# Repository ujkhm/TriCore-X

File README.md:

# Xeltri

> **Xeltri: a heterogeneous development board.**
> X = mixed heterogeneous cores, el = electronics, tri = three cores (MPU + MCU + FPGA).
> This board puts an FPGA, an MPU, and an MCU on one system. (in development)

#### Read the original Traditional Chinese version [here](README.zh-TW.md).

**Hackaday.io Project Page:** [Xeltri - Pick and Place Control Board](https://hackaday.io/project/206451-xeltri-pick-and-place-control-board)

---

### Project overview
This project is a main controller board built for a desktop pick-and-place (PnP) machine. The three cores — STM32H745XIH6 (MCU), XC7A35T-2CSG325C (FPGA), and V851S (MPU) — are locked in and work together. Expansion I/O so far: PCIe 2.1 ×2 (in a PCIe ×4 slot, wired to the FPGA) and a microSD card slot. Everything else is still TBD.

---

### How it started
I needed a pick-and-place machine, but buying one was too expensive, so I decided to build it myself. I was 15 when I started (25 June 2026). It began as a sudden “what if I just try?” thought, and I then committed to it as a long-term project. A lot of what this board needs is something I only know *what it is for*, not something I have actually designed before. I know this is hard, so please keep expectations modest — but it should not be terrible either.

---

### Board architecture and why these cores
Xeltri is built around STM32H745XIH6 (MCU), XC7A35T-2CSG325C (FPGA), and V851S (MPU). I chose this trio because I want to try mixed alignment: pure optical alignment for simple parts (0805, 0402, and similar packages), and a vision camera (OpenCV-style) for complex parts. I also want up-looking / down-looking cameras plus on-device AI for machine-health checks — that is why V851S is in the mix.

I am using pure optical alignment on simple parts because I want industrial on-the-fly (“flying shot”) speed, and the vision hardware that can actually do that is far too expensive. Optical alignment is much cheaper, but it needs real-time performance. The machine is meant to be a box-style CoreXY so it takes less floor space (like a Voron printer), which means a lot of structure and a lot of stepper motors to control. Closed-loop steppers with the servo drive in the motor base are too expensive for me, and the cheap ones are not fast enough. An FPGA can handle that and more — I want the finished machine to be strong, not merely usable. That is how this three-core combination ended up here.

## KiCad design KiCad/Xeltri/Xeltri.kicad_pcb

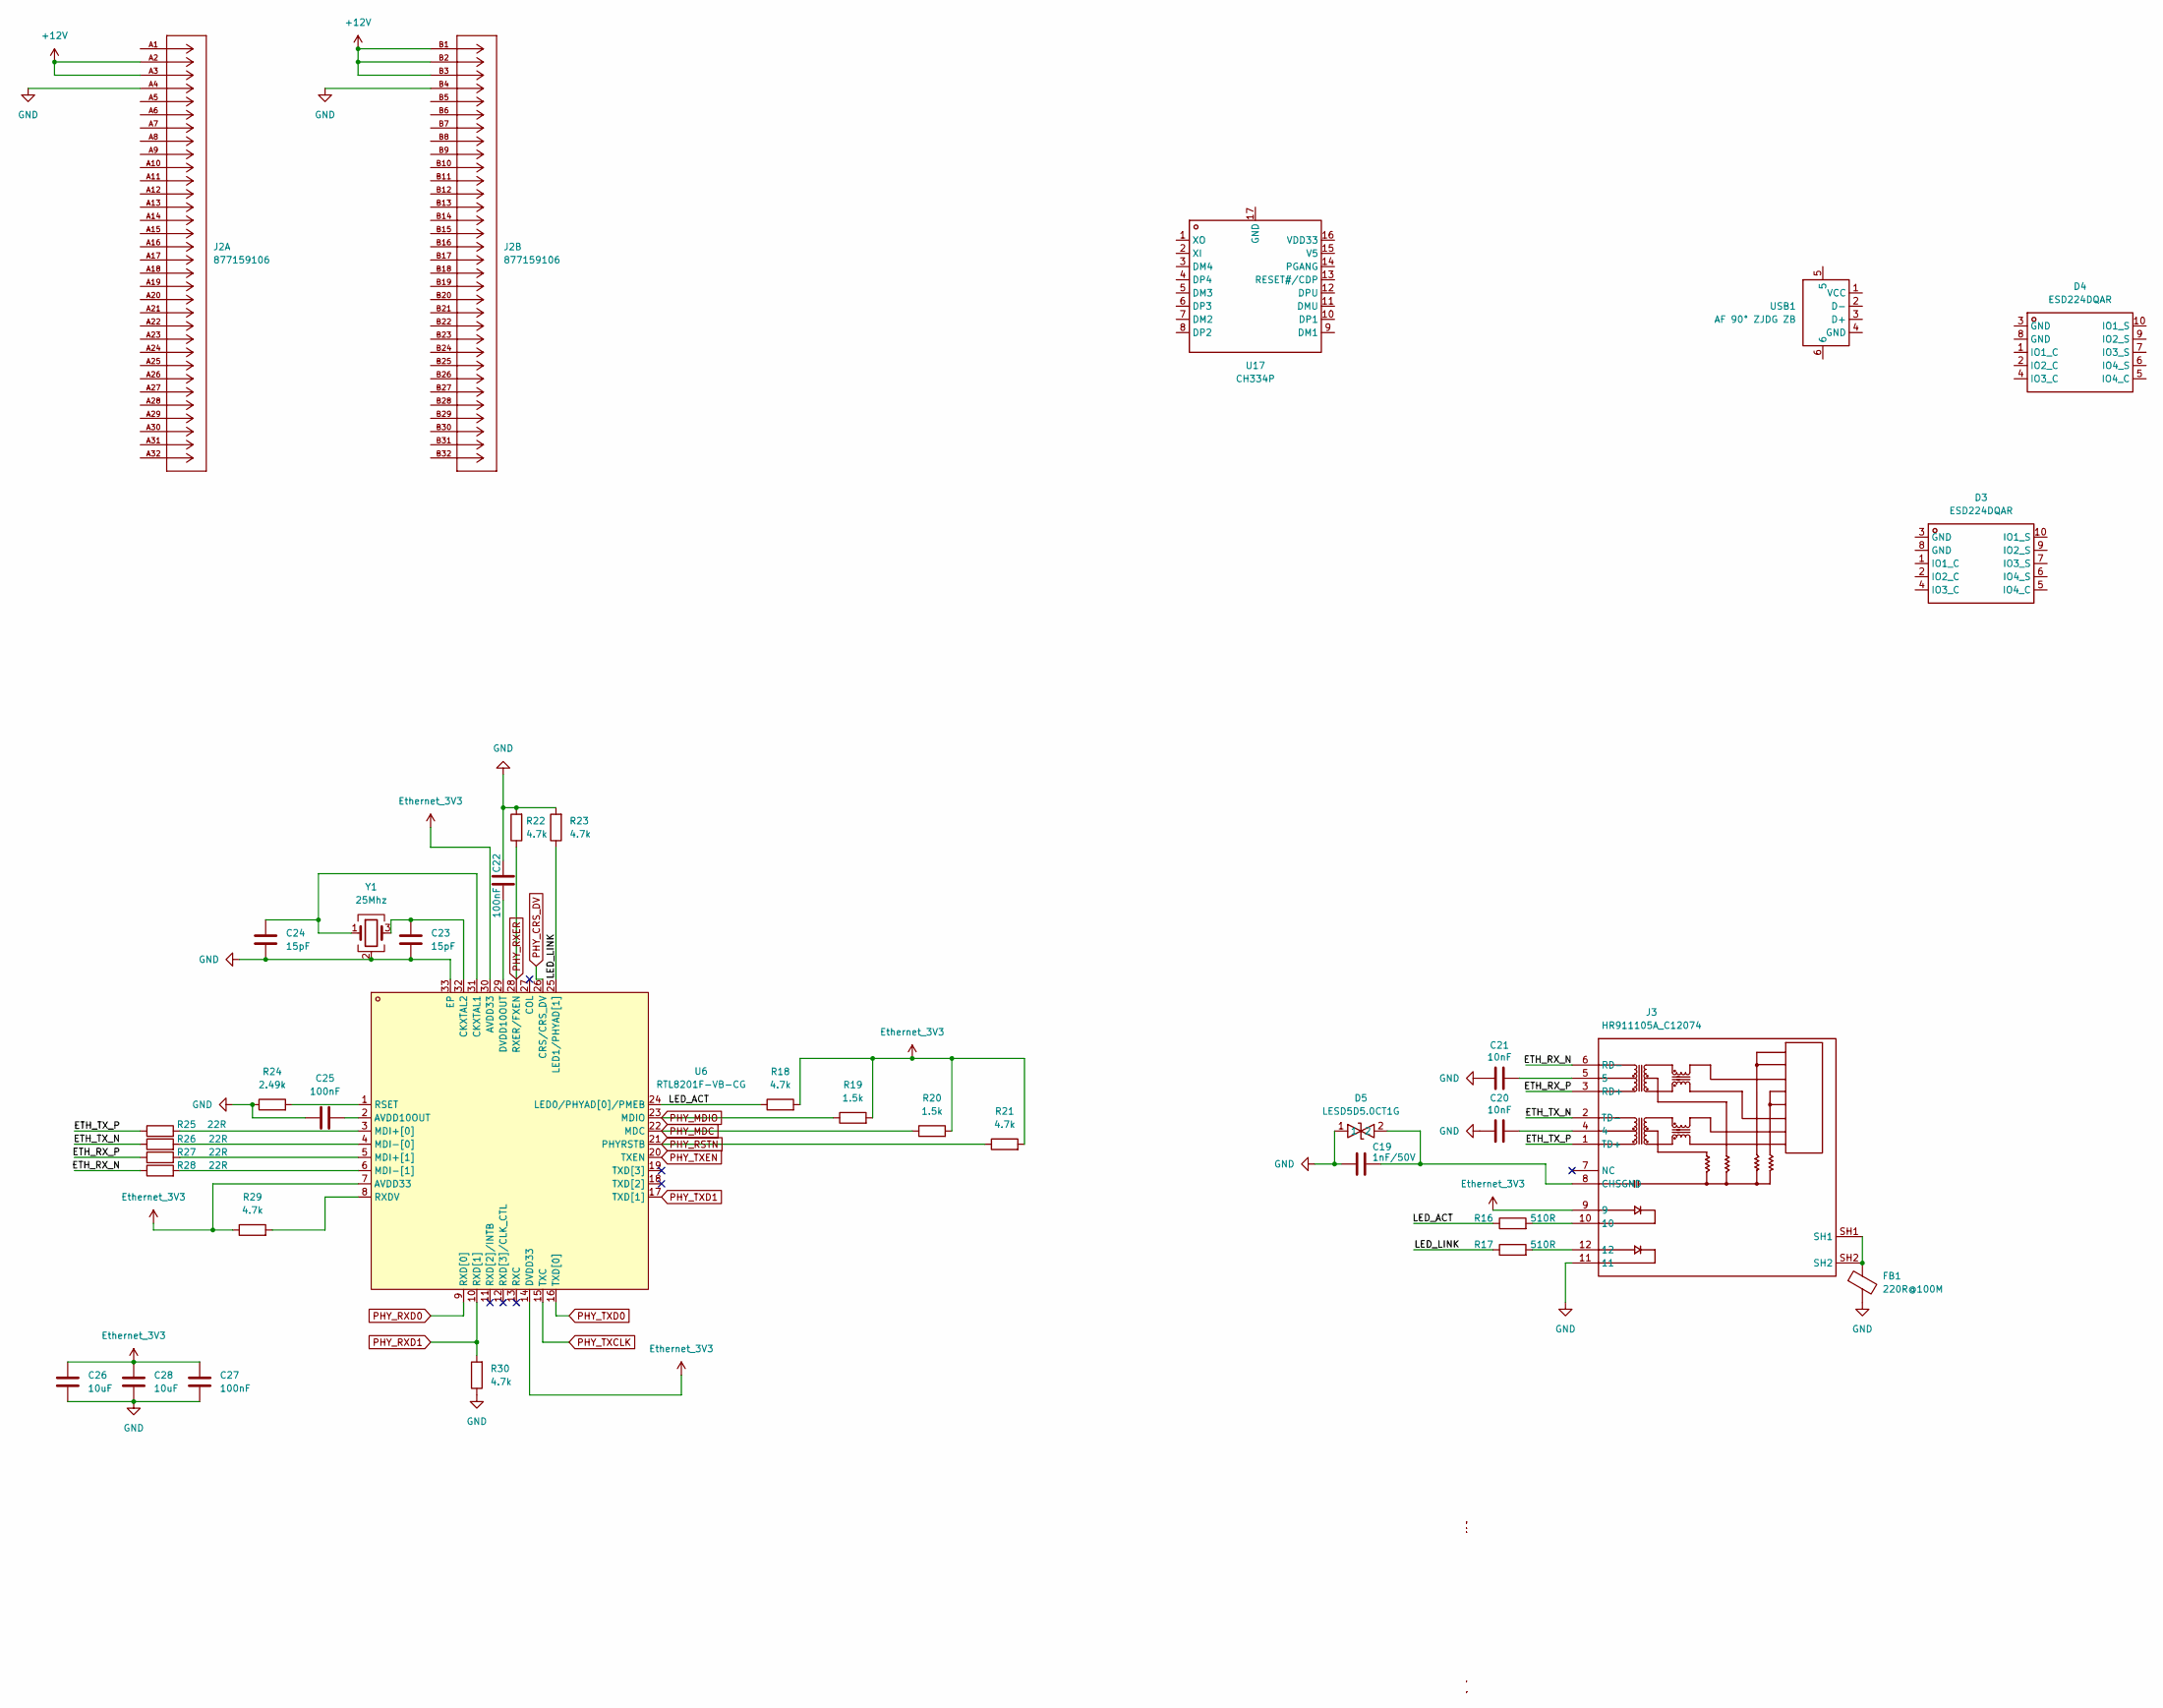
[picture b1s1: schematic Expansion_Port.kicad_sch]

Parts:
C19: 1nF/50V; C_0402_1005Metric
C20, C21: 10nF; C_0402_1005Metric
C22, C25, C27: 100nF; C_0402_1005Metric
C23, C24: 15pF; C_0402_1005Metric
C26, C28: 10uF; C_0402_1005Metric
D3, D4: ESD224DQAR; USON-10_L2.5-W1.0-P0.50-BL; LCSC Part C1981316
D5: LESD5D5.0CT1G; SOD-523_L1.2-W0.8-LS1.6-BI; LCSC Part C383211
FB1: 220R@100M; L_0603_1608Metric
J2: 877159106; CONN_87715-9106_MOL; MANUFACTURER_PART_NUMBER 877159106
J3: HR911105A_C12074; RJ45-TH_HR911105A; LCSC Part C12074
R16, R17: 510R; R_0402_1005Metric
R18, R21, R22, R23, R29, R30: 4.7k; R_0402_1005Metric
R19, R20: 1.5k; R_0402_1005Metric
R24: 2.49k; R_0402_1005Metric
R25, R26, R27, R28: 22R; R_0402_1005Metric
U6: RTL8201F-VB-CG; QFN-32_L5.0-W5.0-P0.50-BL-EP3.4; MPN RTL8201F-VB-CG; LCSC Part C45044
U17: CH334P; QFN-16_L3.0-W3.0-P0.50-BL-EP1.7; LCSC Part C5373042
USB1: AF 90° ZJDG ZB; USB-A-TH_AF-90-ZJDG-ZB; LCSC Part C6332182
Y1: 25Mhz; Crystal_SMD_3225-4Pin_3.2x2.5mm

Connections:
+12V: J2.A2, J2.A3, J2.B1, J2.B2, J2.B3; also elsewhere on the board
/Expansion_Port/ETH_RX_N: J3.6 (RD-), R28.1
/Expansion_Port/ETH_RX_P: J3.3 (RD+), R27.1
/Expansion_Port/ETH_TX_N: J3.2 (TD-), R26.1
/Expansion_Port/ETH_TX_P: J3.1 (TD+), R25.1
/Expansion_Port/LED_ACT: R16.1, R18.1, U6.24 (LED0/PHYAD[0]/PMEB)
/Expansion_Port/LED_LINK: R17.1, R23.1, U6.25 (LED1/PHYAD[1])
Ethernet_3V3: C26.1, C27.1, C28.1, J3.9, R18.2, R19.2, R20.2, R21.2, R29.1, U6.7 (AVDD33), U6.14 (DVDD33), U6.30 (AVDD33)
GND: C19.1, C20.1, C21.1, C22.2, C23.1, C24.1, C25.1, C26.2, C27.2, C28.2, D5.1, FB1.2, J2.A4, J2.B4, J3.11, R22.2, R23.2, R24.1, R30.1, U6.33 (EP), Y1.2 (G), Y1.4 (G); also elsewhere on the board
unnamed: C20.2, J3.4
unnamed: C21.2, J3.5
unnamed: FB1.1, J3.SH1, J3.SH2
unnamed: C19.2, D5.2, J3.8 (CHSGND)
unnamed: J3.10, R16.2
unnamed: J3.12, R17.2
unnamed: C25.2, U6.2 (AVDD10OUT)
unnamed: C24.2, U6.31 (CKXTAL1), Y1.1
unnamed: C23.2, U6.32 (CKXTAL2), Y1.3
unnamed: C22.1, U6.29 (DVDD10OUT)
unnamed: R25.2, U6.3 (MDI+[0])
unnamed: R27.2, U6.5 (MDI+[1])
unnamed: R26.2, U6.4 (MDI-[0])
unnamed: R28.2, U6.6 (MDI-[1])
unnamed: R24.2, U6.1 (RSET)
unnamed: R29.2, U6.8 (RXDV)
PHY_CRS_DV: U6.26 (CRS/CRS_DV)
PHY_MDC: R20.1, U6.22 (MDC)
PHY_MDIO: R19.1, U6.23 (MDIO)
PHY_RSTN: R21.1, U6.21 (PHYRSTB)
PHY_RXD0: U6.9 (RXD[0])
PHY_RXD1: R30.2, U6.10 (RXD[1])
PHY_RXER: R22.1, U6.28 (RXER/FXEN)
PHY_TXCLK: U6.15 (TXC)
PHY_TXD0: U6.16 (TXD[0])
PHY_TXD1: U6.17 (TXD[1])
PHY_TXEN: U6.20 (TXEN)

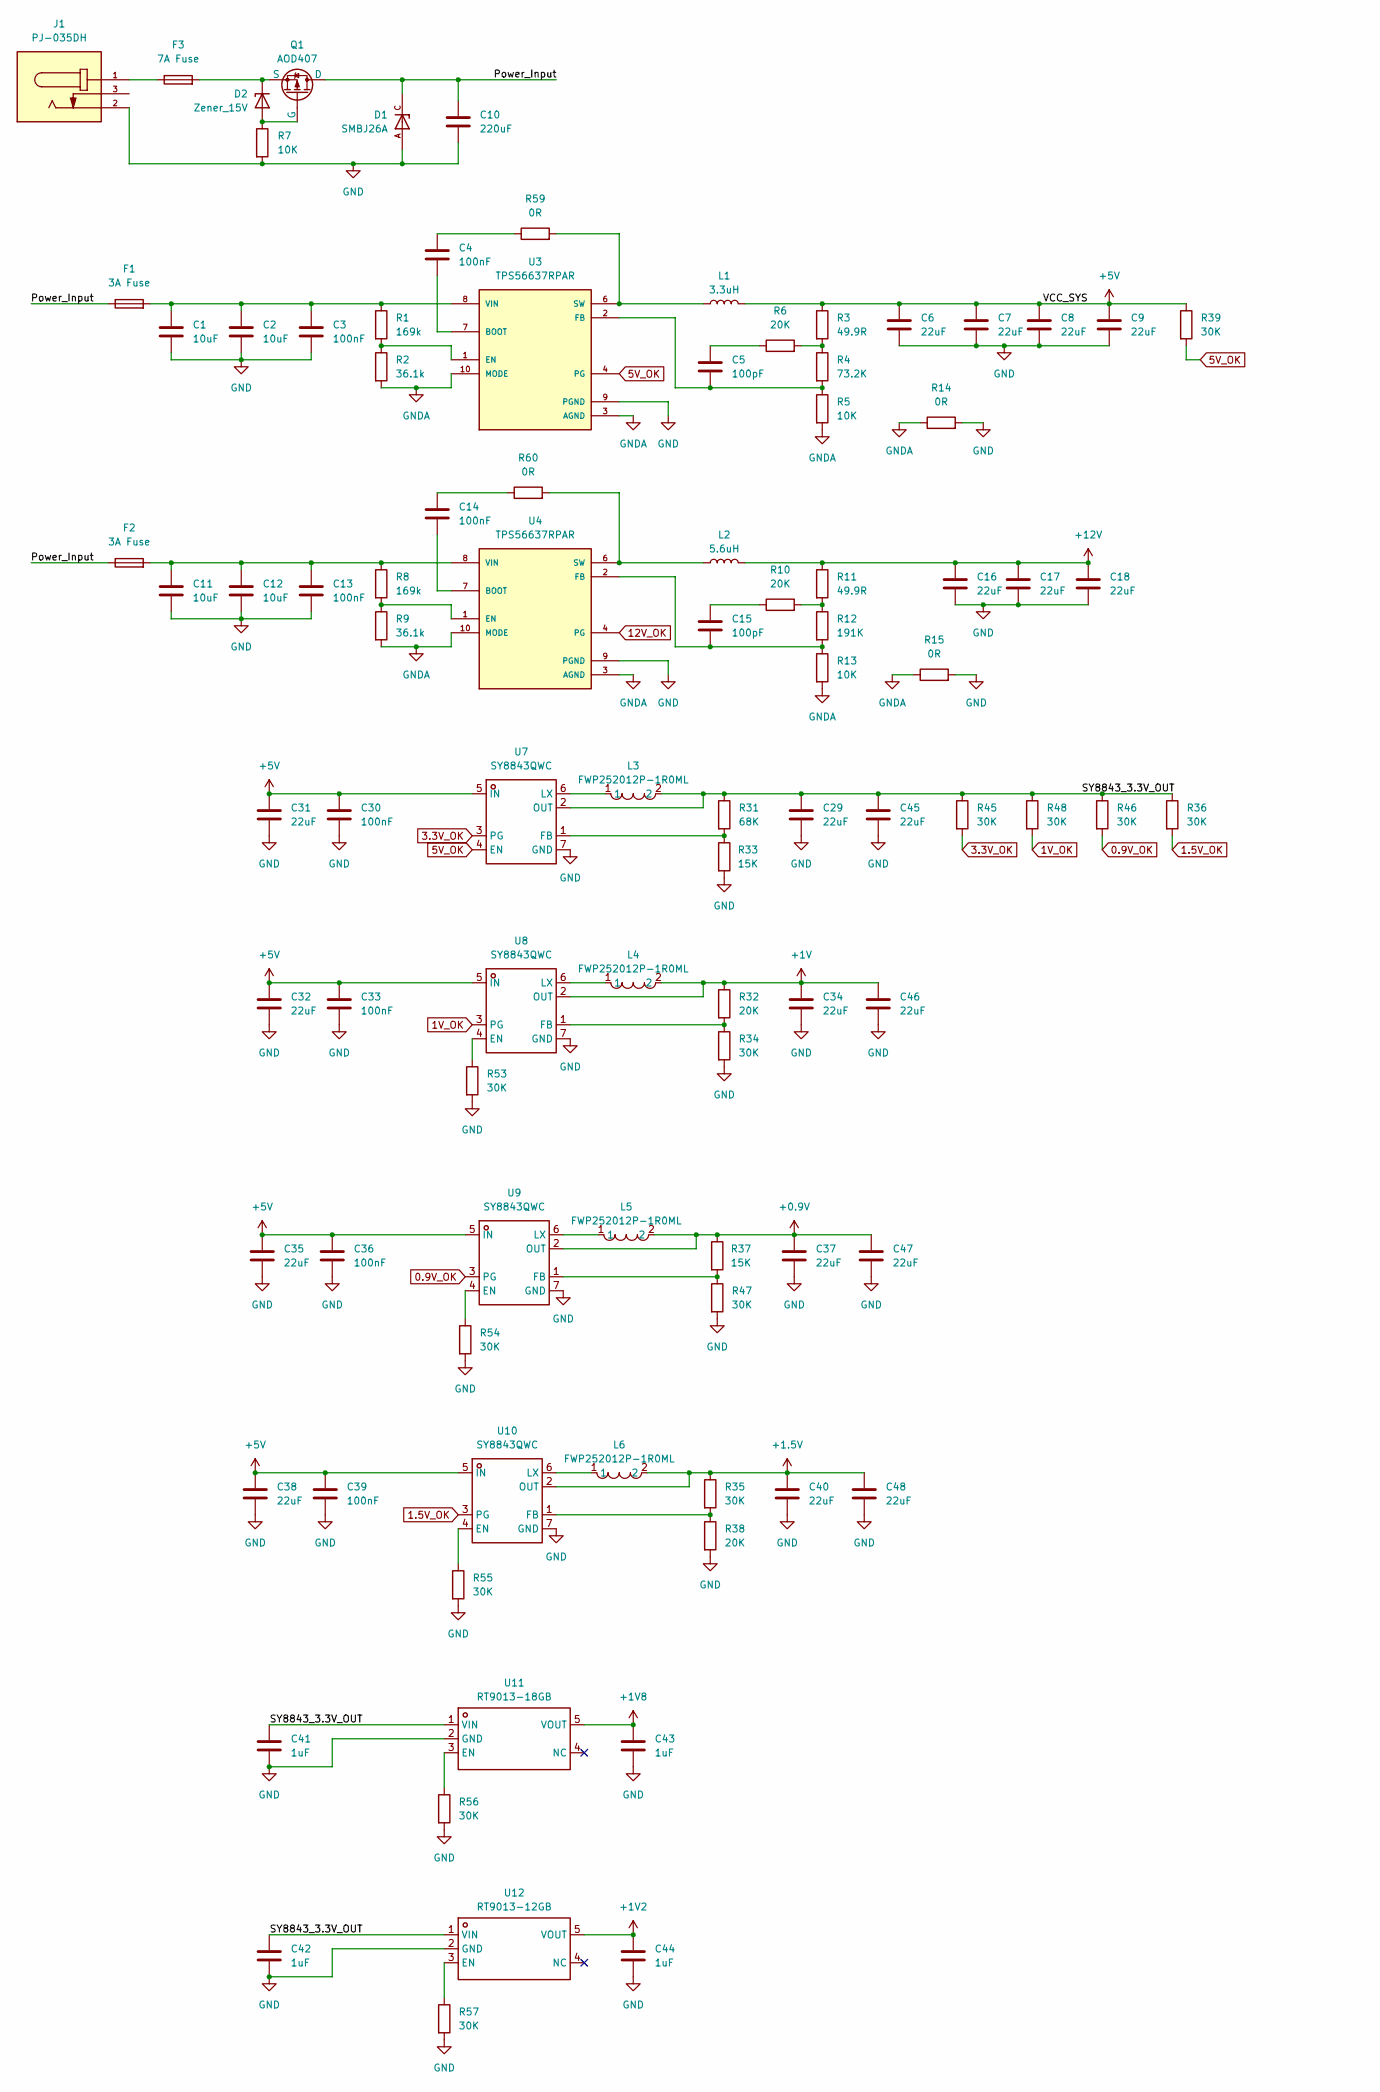
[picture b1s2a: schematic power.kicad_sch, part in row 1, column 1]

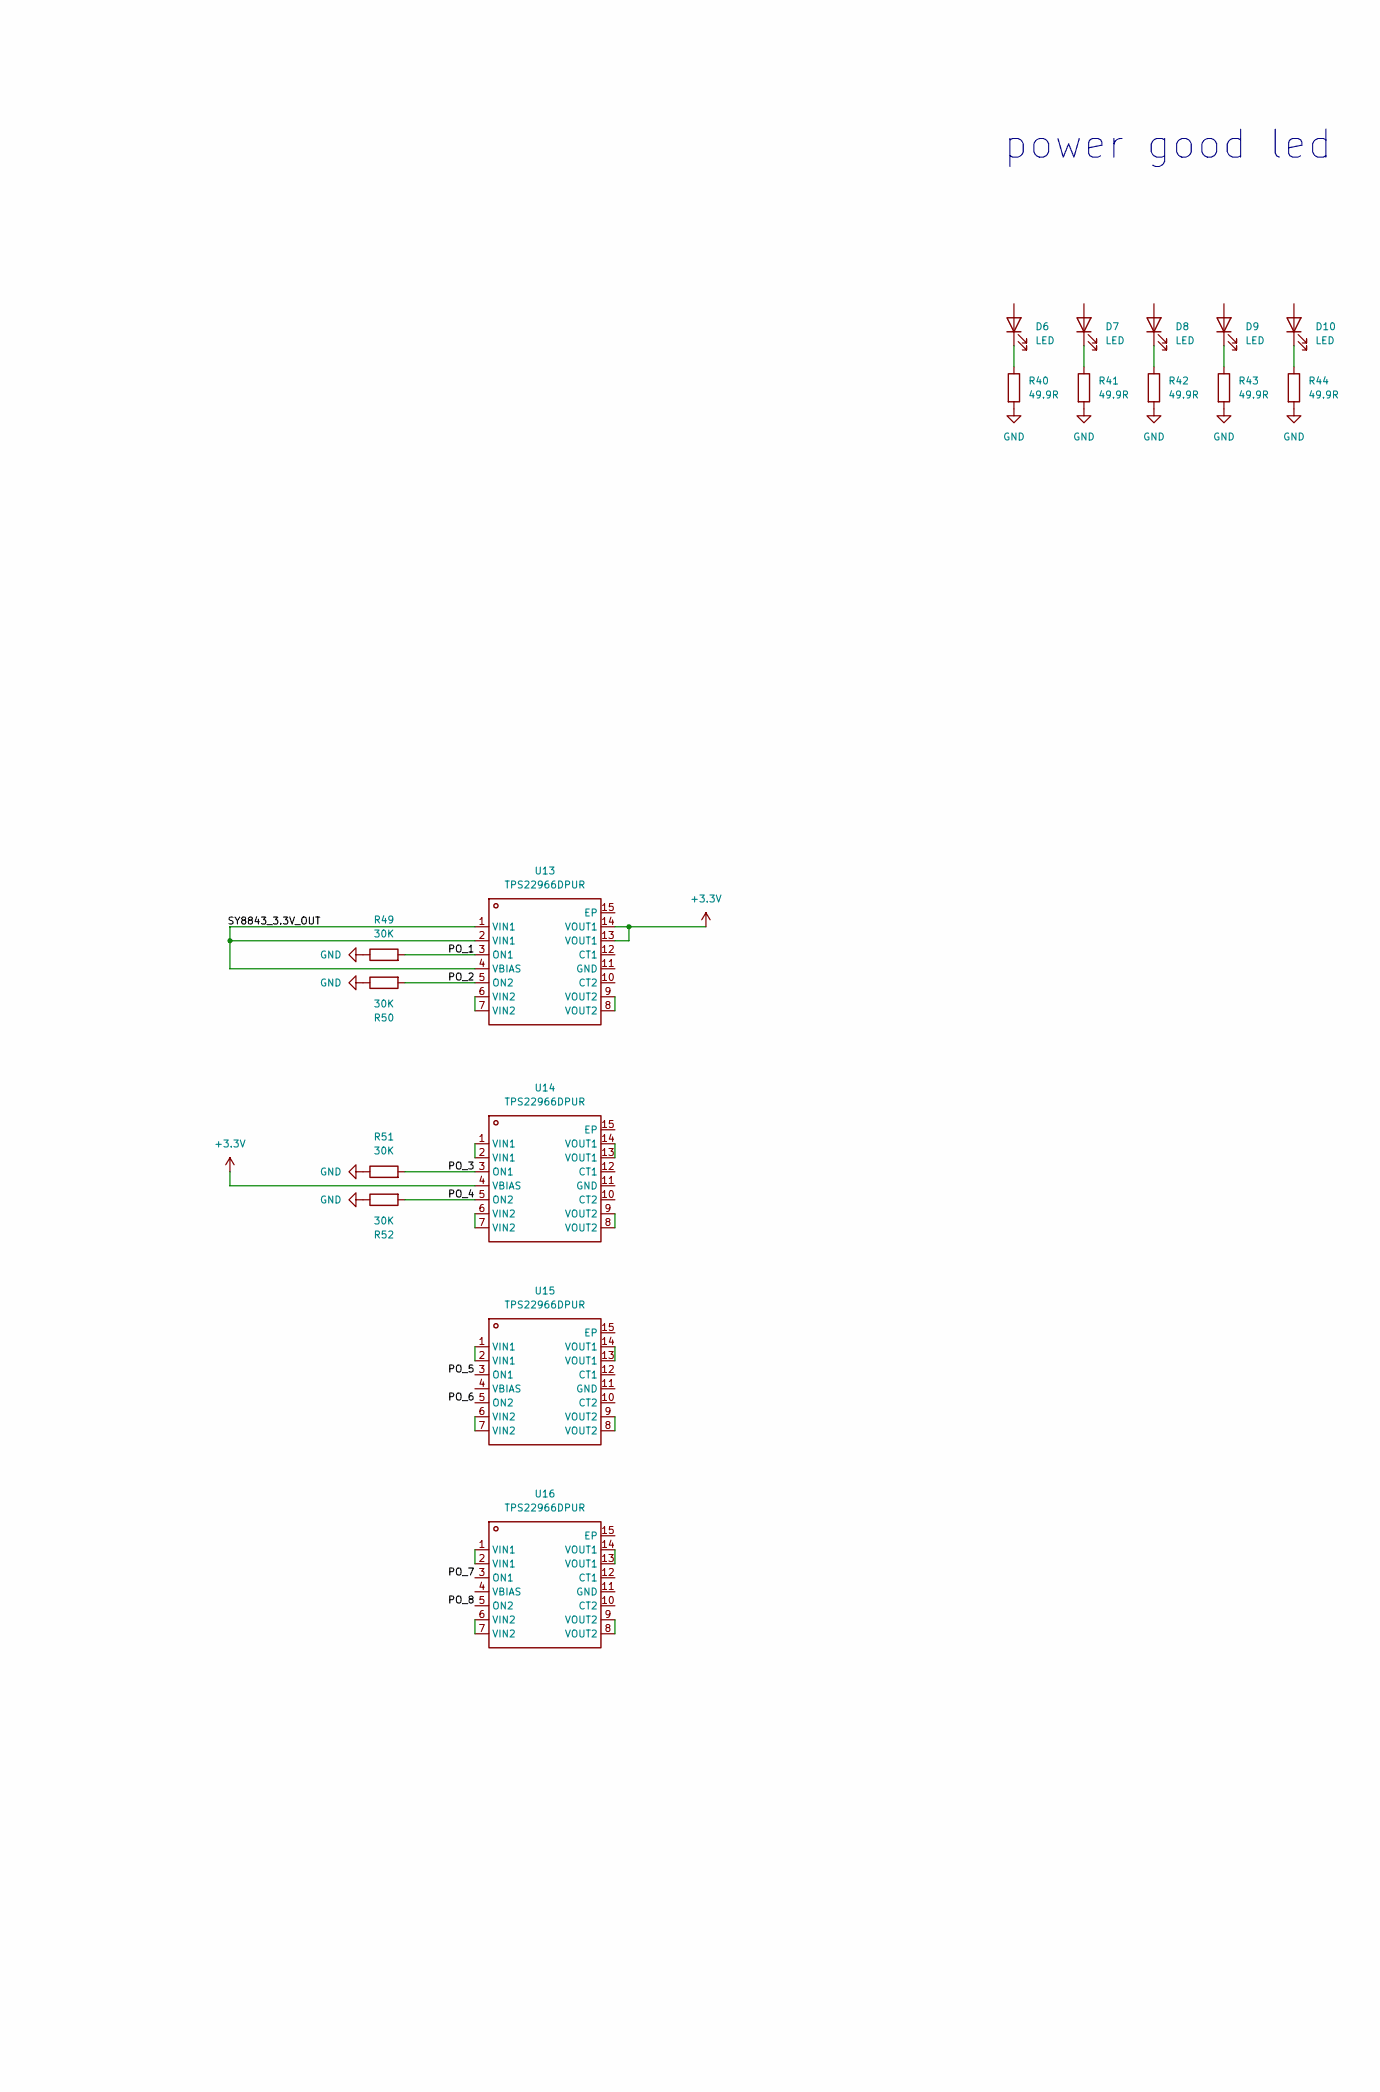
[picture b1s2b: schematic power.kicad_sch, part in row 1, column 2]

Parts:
C1, C2, C11, C12: 10uF; C_1210_3225Metric
C3, C13: 100nF; C_0805_2012Metric
C4, C14, C30, C33, C36, C39: 100nF; C_0402_1005Metric
C5, C15: 100pF; C_0402_1005Metric
C6, C7, C8, C9, C16, C17, C18, C29, C31, C32, C34, C35, C37, C38, C40, C45, C46, C47, C48: 22uF; C_0805_2012Metric
C10: 220uF; C_Elec_8x10.2
C41, C42, C43, C44: 1uF; C_0402_1005Metric
D1: SMBJ26A; DIOM4336X265N; PARTREV F2102
D2: Zener_15V; D_SOD-123
D6, D7, D8, D9, D10: LED; LED_0603_1608Metric
F1, F2: 3A Fuse; Fuse_1206_3216Metric
F3: 7A Fuse; Fuse_1206_3216Metric
J1: PJ-035DH; CUI_PJ-035DH; PARTREV 1.05
L1: 3.3uH; L_Bourns_SRP7028A_7.3x6.6mm
L2: 5.6uH; L_Bourns_SRP7028A_7.3x6.6mm
L3, L4, L5, L6: FWP252012P-1R0ML; IND-SMD_L2.5-W2.0_YXMBL252010P; LCSC Part C5179444
Q1: AOD407; TO-252-2
R1, R8: 169k; R_0402_1005Metric
R2, R9: 36.1k; R_0402_1005Metric
R3, R11, R40, R41, R42, R43, R44: 49.9R; R_0402_1005Metric
R4: 73.2K; R_0402_1005Metric
R5, R7, R13: 10K; R_0402_1005Metric
R6, R10, R32, R38: 20K; R_0402_1005Metric
R12: 191K; R_0402_1005Metric
R14, R15, R59, R60: 0R; R_0402_1005Metric
R31: 68K; R_0402_1005Metric
R33, R37: 15K; R_0402_1005Metric
R34, R35, R36, R39, R45, R46, R47, R48, R49, R50, R51, R52, R53, R54, R55, R56, R57: 30K; R_0402_1005Metric
U3, U4: TPS56637RPAR; CONV_TPS56637RPAR; PARTREV A
U7, U8, U9, U10: SY8843QWC; QFN-7_L1.5-W1.5-P0.45-BL_SILERGY_SY8842QWC; LCSC Part C3151906
U11: RT9013-18GB; SOT-23-5_L3.0-W1.7-P0.95-LS2.8-BR; LCSC Part C59969
U12: RT9013-12GB; SOT-23-5_L3.0-W1.7-P0.95-LS2.8-BR; LCSC Part C58464
U13, U14, U15, U16: TPS22966DPUR; WSON-14_L3.0-W2.0-P0.40-BL-EP; LCSC Part C398913

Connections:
0.9V_OK: R46.2, U9.3 (PG)
1.5V_OK: R36.2, U10.3 (PG)
1V_OK: R48.2, U8.3 (PG)
3.3V_OK: R45.2, U7.3 (PG)
5V_OK: R39.2, U3.4 (PG), U7.4 (EN)
12V_OK: U4.4 (PG)
+0.9V: C37.1, C47.1, L5.2, R37.1, U9.2 (OUT)
+1.5V: C40.1, C48.1, L6.2, R35.1, U10.2 (OUT)
+1V: C34.1, C46.1, L4.2, R32.1, U8.2 (OUT)
+1V2: C44.1, U12.5 (VOUT)
+1V8: C43.1, U11.5 (VOUT)
+3.3V: U13.13 (VOUT1), U13.14 (VOUT1), U14.4 (VBIAS); also elsewhere on the board
+5V: C6.1, C7.1, C8.1, C9.1, C30.1, C31.1, C32.1, C33.1, C35.1, C36.1, C38.1, C39.1, L1.2, R3.1, R39.1, U7.5 (IN), U8.5 (IN), U9.5 (IN), U10.5 (IN)
+12V: C16.1, C17.1, C18.1, L2.2, R11.1; also elsewhere on the board
/power/PO_1: R49.2, U13.3 (ON1)
/power/PO_2: R50.2, U13.5 (ON2)
/power/PO_3: R51.2, U14.3 (ON1)
/power/PO_4: R52.2, U14.5 (ON2)
/power/PO_5: U15.3 (ON1)
/power/PO_6: U15.5 (ON2)
/power/PO_7: U16.3 (ON1)
/power/PO_8: U16.5 (ON2)
/power/Power_Input: C10.1, D1.C, F1.1, F2.1, Q1.1 (D)
/power/SY8843_3.3V_OUT: C29.1, C41.1, C42.1, C45.1, L3.2, R31.1, R36.1, R45.1, R46.1, R48.1, U7.2 (OUT), U11.1 (VIN), U12.1 (VIN), U13.1 (VIN1), U13.2 (VIN1), U13.4 (VBIAS)
GND: C1.2, C2.2, C3.2, C6.2, C7.2, C8.2, C9.2, C10.2, C11.2, C12.2, C13.2, C16.2, C17.2, C18.2, C29.2, C30.2, C31.2, C32.2, C33.2, C34.2, C35.2, C36.2, C37.2, C38.2, C39.2, C40.2, C41.2, C42.2, C43.2, C44.2, C45.2, C46.2, C47.2, C48.2, D1.A, J1.2, R7.2, R14.2, R15.2, R33.2, R34.2, R38.2, R40.2, R41.2, R42.2, R43.2, R44.2, R47.2, R49.1, R50.1, R51.1, R52.1, R53.2, R54.2, R55.2, R56.2, R57.2, U3.9 (PGND), U4.9 (PGND), U7.7 (GND), U8.7 (GND), U9.7 (GND), U10.7 (GND), U11.2 (GND), U12.2 (GND); also elsewhere on the board
GNDA: R2.2, R5.2, R9.2, R13.2, R14.1, R15.1, U3.3 (AGND), U3.10 (MODE), U4.3 (AGND), U4.10 (MODE)
unnamed: C4.2, R59.1
unnamed: C5.1, R6.1
unnamed: C14.2, R60.1
unnamed: C15.1, R10.1
unnamed: D2.2 (A), Q1.2 (G), R7.1
unnamed: D2.1 (K), F3.2, Q1.3 (S)
unnamed: D6.1 (K), R40.1
unnamed: D7.1 (K), R41.1
unnamed: D8.1 (K), R42.1
unnamed: D9.1 (K), R43.1
unnamed: D10.1 (K), R44.1
unnamed: F3.1, J1.1
unnamed: R3.2, R4.1, R6.2
unnamed: R10.2, R11.2, R12.1
unnamed: C4.1, U3.7 (BOOT)
unnamed: R1.2, R2.1, U3.1 (EN)
unnamed: C5.2, R4.2, R5.1, U3.2 (FB)
unnamed: L1.1, R59.2, U3.6 (SW)
unnamed: C1.1, C2.1, C3.1, F1.2, R1.1, U3.8 (VIN)
unnamed: C14.1, U4.7 (BOOT)
unnamed: R8.2, R9.1, U4.1 (EN)
unnamed: C15.2, R12.2, R13.1, U4.2 (FB)
unnamed: L2.1, R60.2, U4.6 (SW)
unnamed: C11.1, C12.1, C13.1, F2.2, R8.1, U4.8 (VIN)
unnamed: R31.2, R33.1, U7.1 (FB)
unnamed: L3.1, U7.6 (LX)
unnamed: R53.1, U8.4 (EN)
unnamed: R32.2, R34.1, U8.1 (FB)
unnamed: L4.1, U8.6 (LX)
unnamed: R54.1, U9.4 (EN)
unnamed: R37.2, R47.1, U9.1 (FB)
unnamed: L5.1, U9.6 (LX)
unnamed: R55.1, U10.4 (EN)
unnamed: R35.2, R38.1, U10.1 (FB)
unnamed: L6.1, U10.6 (LX)
unnamed: R56.1, U11.3 (EN)
unnamed: R57.1, U12.3 (EN)
unnamed: U13.6 (VIN2), U13.7 (VIN2)
unnamed: U13.8 (VOUT2), U13.9 (VOUT2)
unnamed: U14.1 (VIN1), U14.2 (VIN1)
unnamed: U14.6 (VIN2), U14.7 (VIN2)
unnamed: U14.13 (VOUT1), U14.14 (VOUT1)
unnamed: U14.8 (VOUT2), U14.9 (VOUT2)
unnamed: U15.1 (VIN1), U15.2 (VIN1)
unnamed: U15.6 (VIN2), U15.7 (VIN2)
unnamed: U15.13 (VOUT1), U15.14 (VOUT1)
unnamed: U15.8 (VOUT2), U15.9 (VOUT2)
unnamed: U16.1 (VIN1), U16.2 (VIN1)
unnamed: U16.6 (VIN2), U16.7 (VIN2)
unnamed: U16.13 (VOUT1), U16.14 (VOUT1)
unnamed: U16.8 (VOUT2), U16.9 (VOUT2)

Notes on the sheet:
power good led

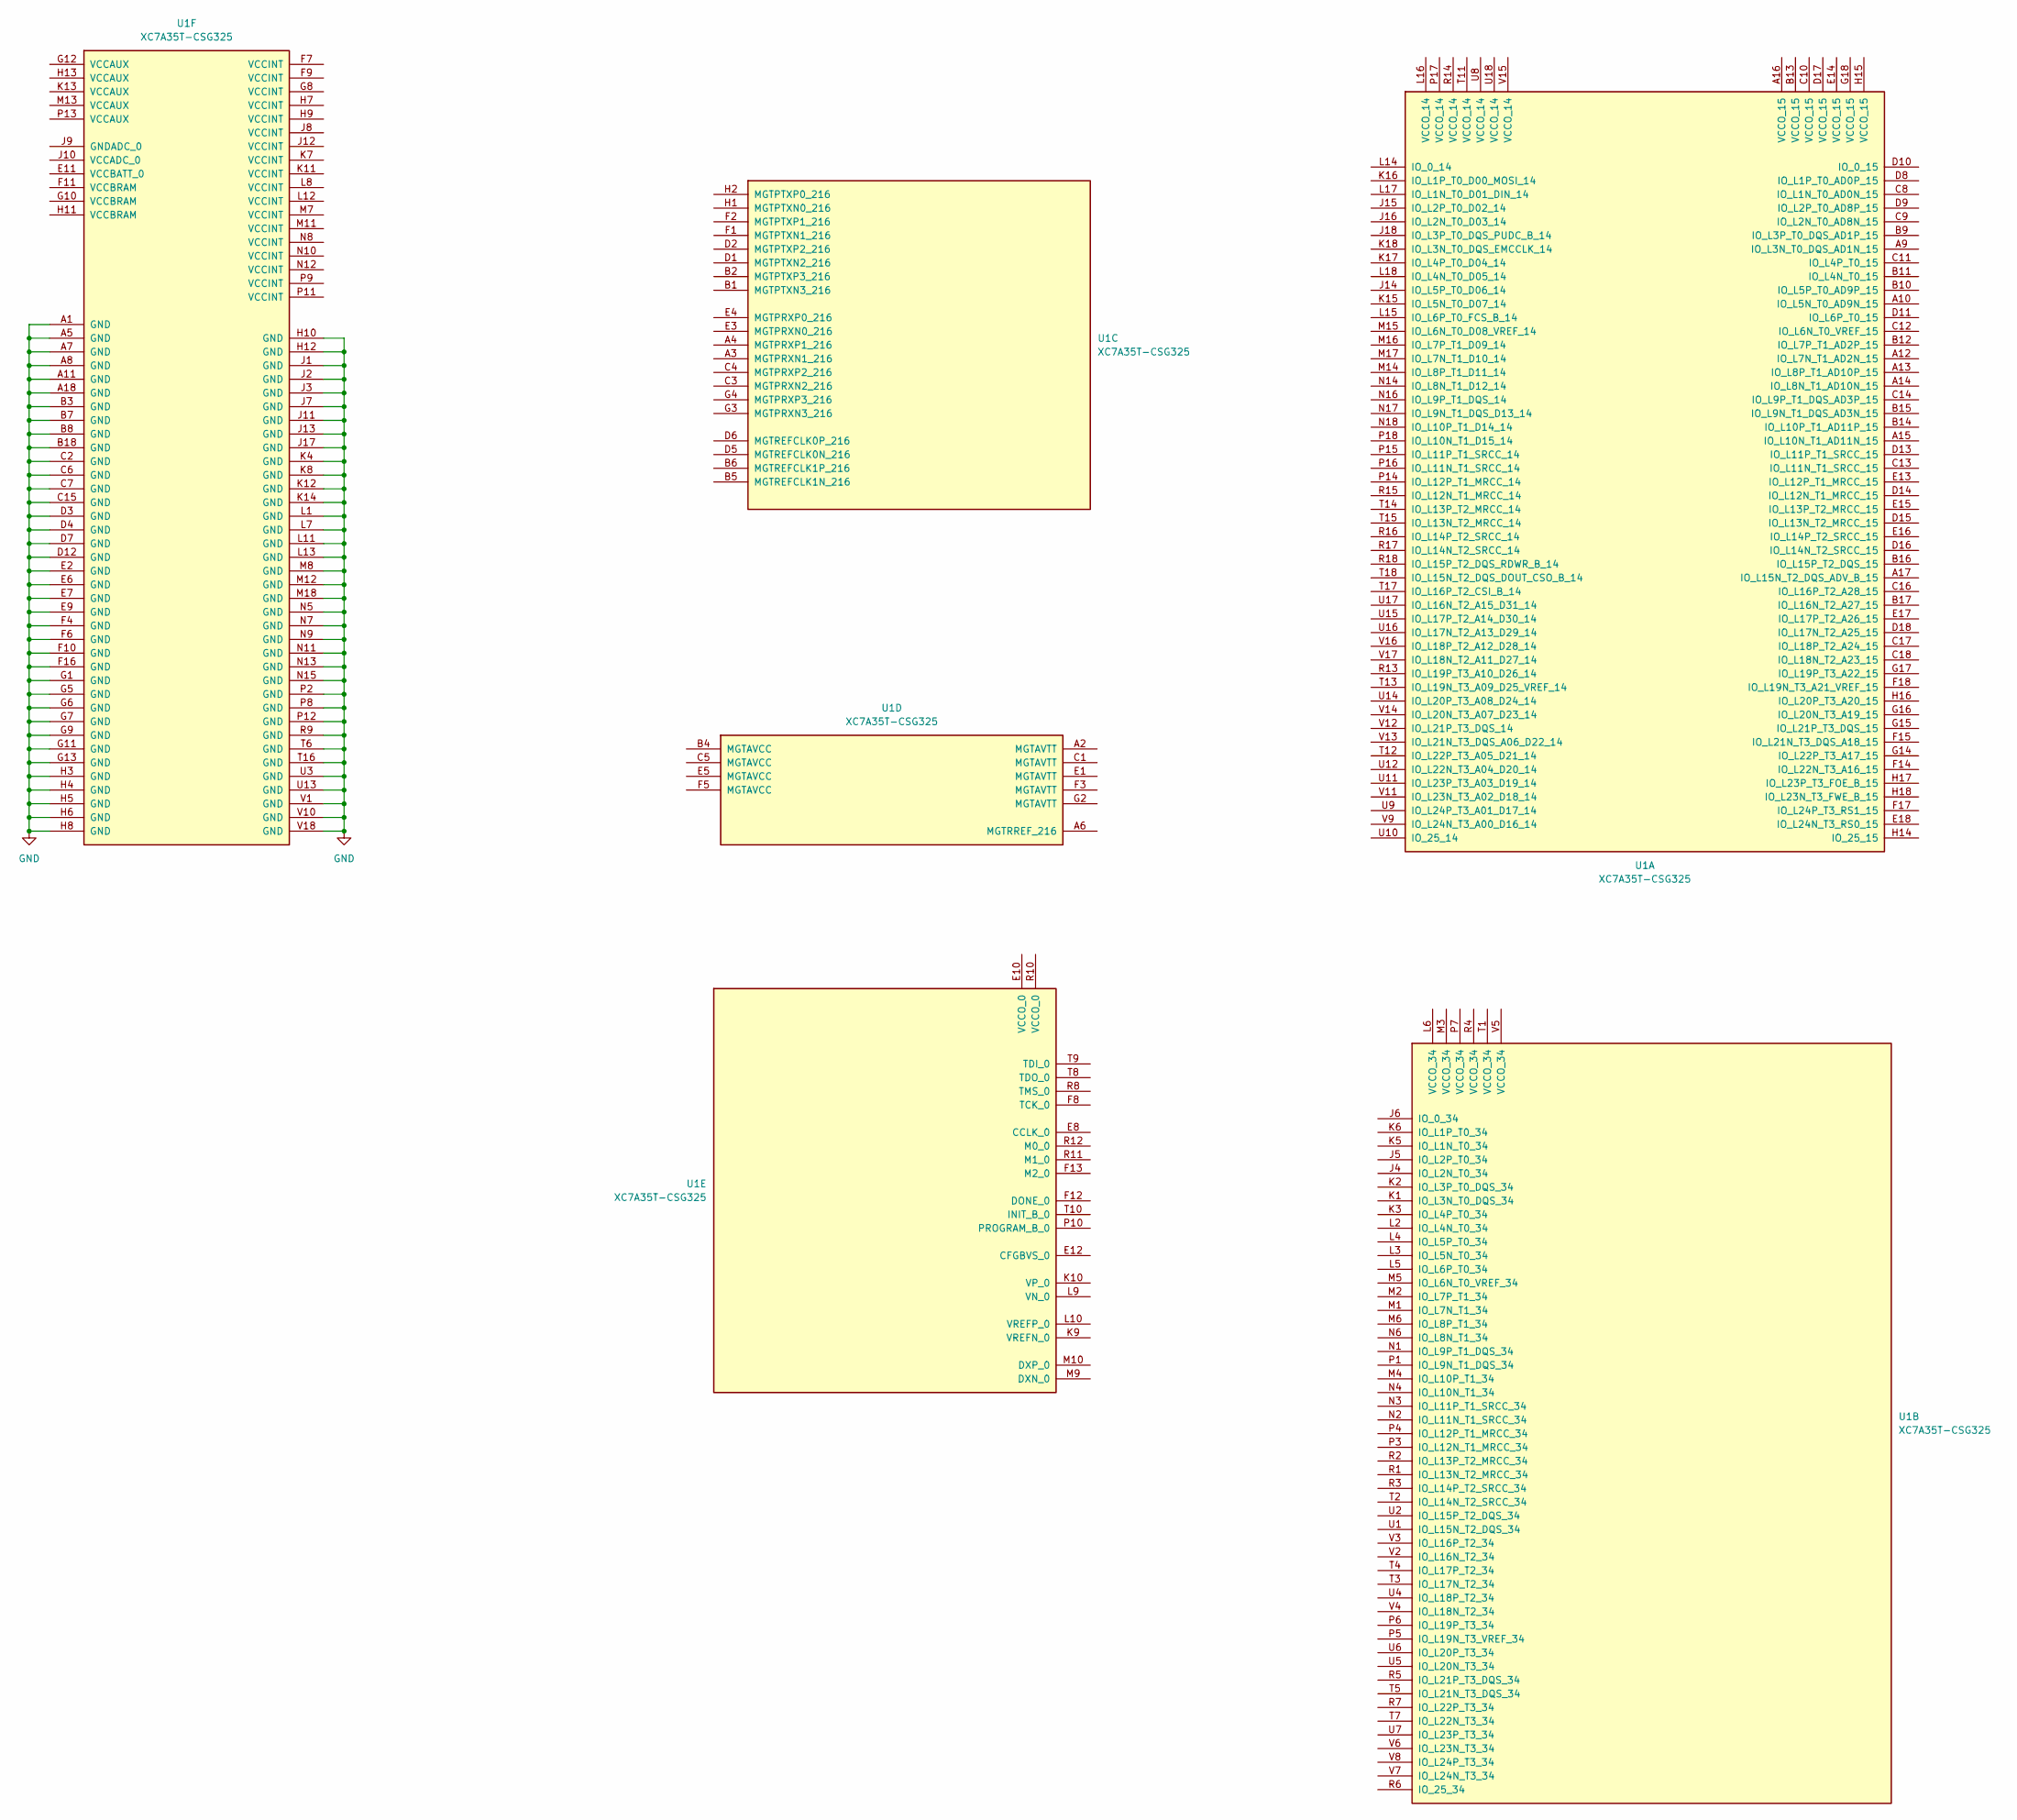
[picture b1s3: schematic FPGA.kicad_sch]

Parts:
U1: XC7A35T-CSG325; Xilinx_CSG325

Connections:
GND: U1.A1 (GND), U1.A5 (GND), U1.A7 (GND), U1.A8 (GND), U1.A11 (GND), U1.A18 (GND), U1.B3 (GND), U1.B7 (GND), U1.B8 (GND), U1.B18 (GND), U1.C2 (GND), U1.C6 (GND), U1.C7 (GND), U1.C15 (GND), U1.D3 (GND), U1.D4 (GND), U1.D7 (GND), U1.D12 (GND), U1.E2 (GND), U1.E6 (GND), U1.E7 (GND), U1.E9 (GND), U1.F4 (GND), U1.F6 (GND), U1.F10 (GND), U1.F16 (GND), U1.G1 (GND), U1.G5 (GND), U1.G6 (GND), U1.G7 (GND), U1.G9 (GND), U1.G11 (GND), U1.G13 (GND), U1.H3 (GND), U1.H4 (GND), U1.H5 (GND), U1.H6 (GND), U1.H8 (GND), U1.H10 (GND), U1.H12 (GND), U1.J1 (GND), U1.J2 (GND), U1.J3 (GND), U1.J7 (GND), U1.J11 (GND), U1.J13 (GND), U1.J17 (GND), U1.K4 (GND), U1.K8 (GND), U1.K12 (GND), U1.K14 (GND), U1.L1 (GND), U1.L7 (GND), U1.L11 (GND), U1.L13 (GND), U1.M8 (GND), U1.M12 (GND), U1.M18 (GND), U1.N5 (GND), U1.N7 (GND), U1.N9 (GND), U1.N11 (GND), U1.N13 (GND), U1.N15 (GND), U1.P2 (GND), U1.P8 (GND), U1.P12 (GND), U1.R9 (GND), U1.T6 (GND), U1.T16 (GND), U1.U3 (GND), U1.U13 (GND), U1.V1 (GND), U1.V10 (GND), U1.V18 (GND); also elsewhere on the board

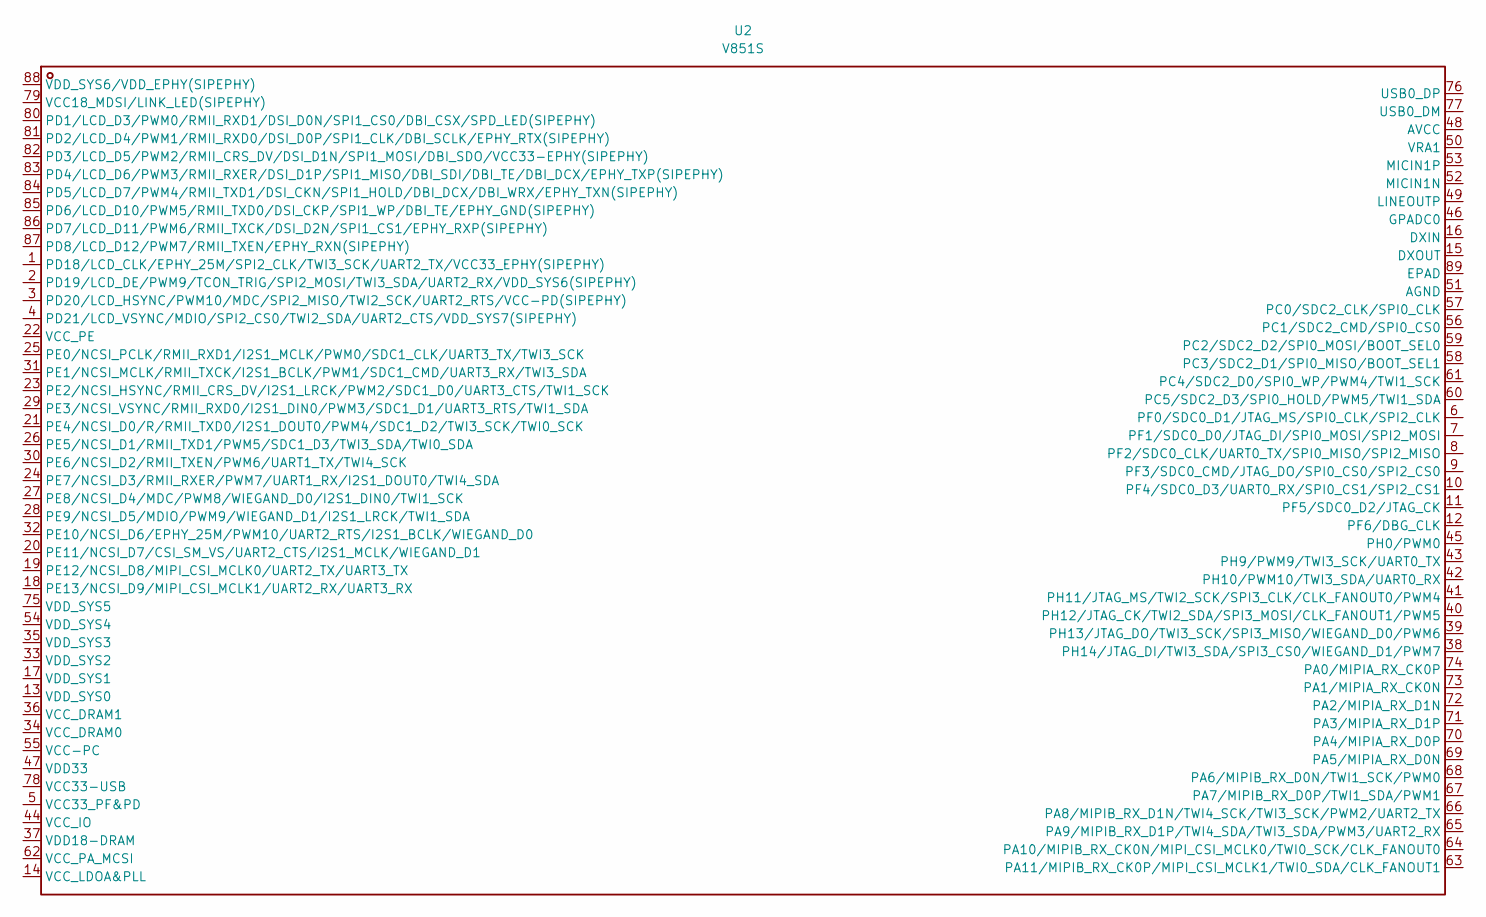
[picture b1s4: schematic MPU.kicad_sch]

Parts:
U2: V851S; QFN-88_L9.0-W9.0-P0.35-TL-EP6.5; LCSC Part C5365286
